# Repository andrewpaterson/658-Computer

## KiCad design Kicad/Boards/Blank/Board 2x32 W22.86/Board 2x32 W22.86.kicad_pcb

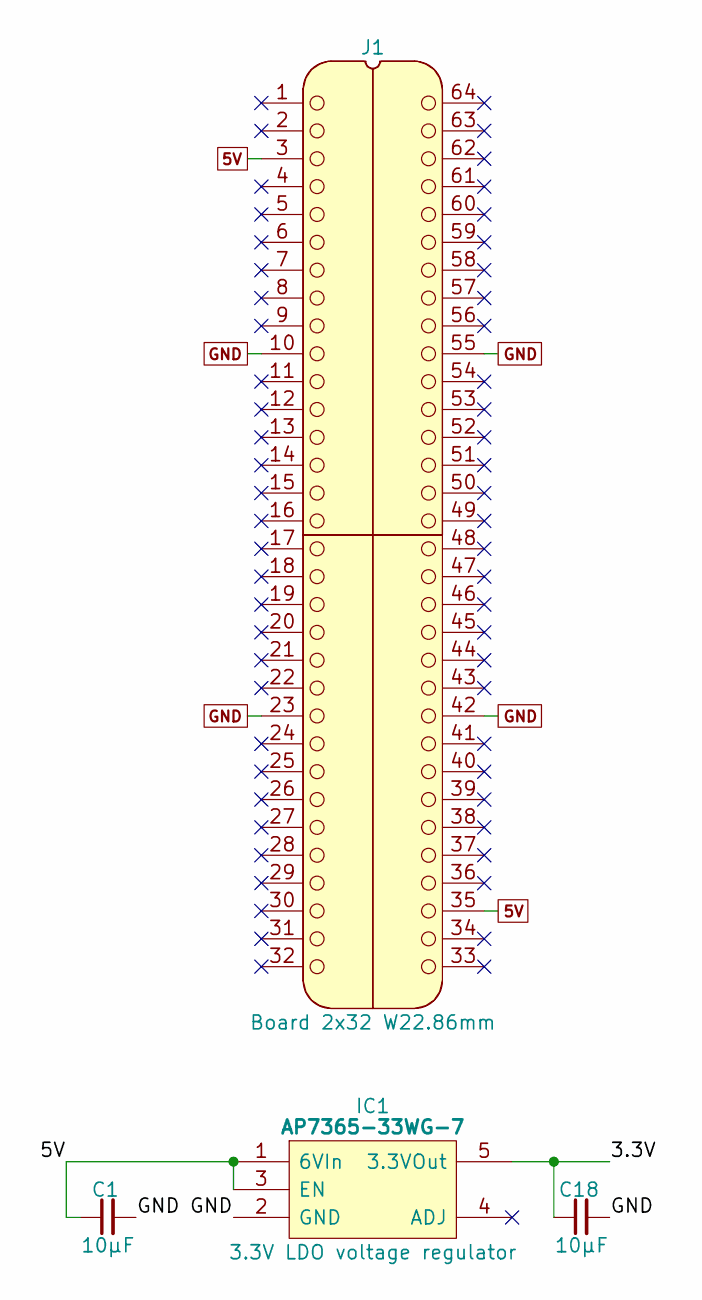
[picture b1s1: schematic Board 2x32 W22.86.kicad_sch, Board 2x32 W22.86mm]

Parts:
C1, C18: 10µF; C_0805
IC1: AP7365-33WG-7; SOT95P285X130-5N; Manufacturer_Part_Number AP7365-33WG-7; Mouser Part Number 621-AP7365-33WG-7
J1: Board 2x32 W22.86mm; DIP-64_Board_W22.86mm

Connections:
5V: C1.1, IC1.1 (6VIn), IC1.3 (EN), J1.3, J1.35
/3.3V: C18.1, IC1.5 (3.3VOut)
GND: C1.2, C18.2, IC1.2 (GND), J1.10, J1.23, J1.42, J1.55

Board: 2 copper layers, 4 parts (0 on the bottom side), 3 nets, no tracks yet.

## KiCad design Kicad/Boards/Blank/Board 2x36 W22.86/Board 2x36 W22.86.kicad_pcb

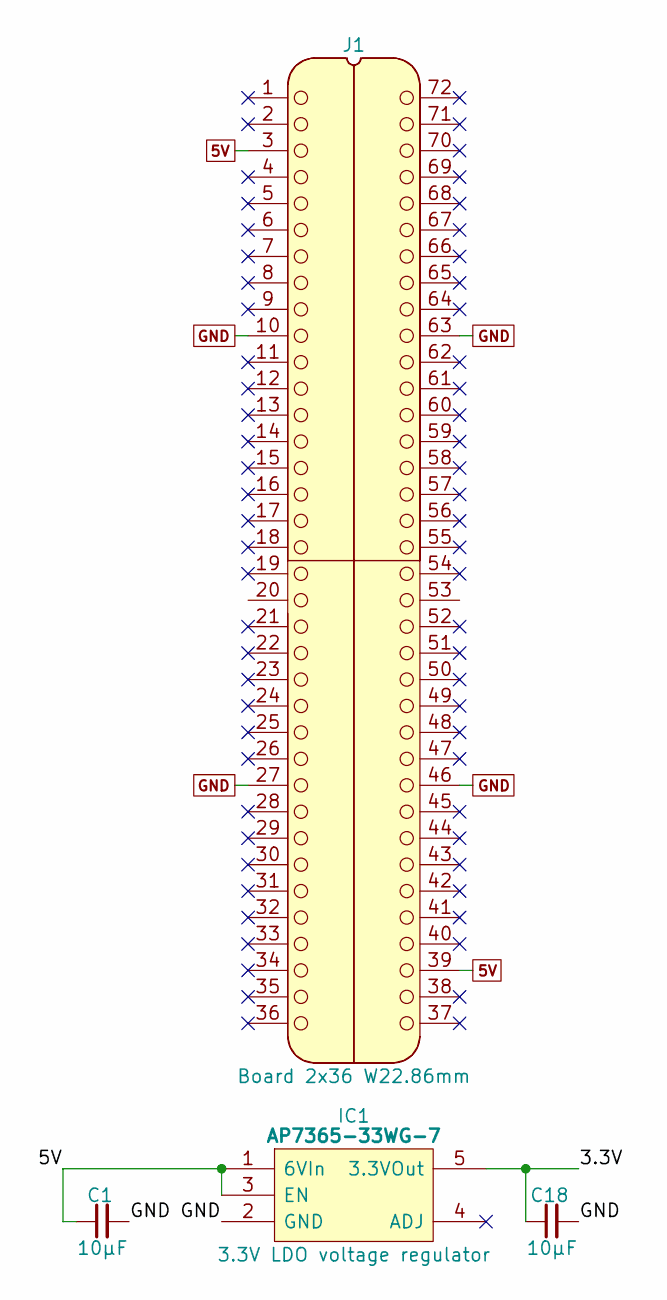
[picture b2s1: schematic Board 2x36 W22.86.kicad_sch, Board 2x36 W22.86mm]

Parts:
C1, C18: 10µF; C_0805
IC1: AP7365-33WG-7; SOT95P285X130-5N; Manufacturer_Part_Number AP7365-33WG-7; Mouser Part Number 621-AP7365-33WG-7
J1: Board 2x36 W22.86mm; DIP-72_Board_W22.86mm

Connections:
5V: C1.1, IC1.1 (6VIn), IC1.3 (EN), J1.3, J1.39
/3.3V: C18.1, IC1.5 (3.3VOut)
GND: C1.2, C18.2, IC1.2 (GND), J1.10, J1.27, J1.46, J1.63

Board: 2 copper layers, 4 parts (0 on the bottom side), 3 nets, no tracks yet.
